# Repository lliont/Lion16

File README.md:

# Lion
Lion FPGA CPU/Computer

The Lion computer project files.

Lion CPU is a homebrew CPU and Lion Computer is a homebrew 16-bit computer based on this cpu.

lionsys.sof and lionsys.jic are the files for configuration of a QMTech Cyclone V FPGA board for Lion.

sdcard.zip contains files for the 30MB FAT partition on a SDCard for Lion to boot.

Lionasm.exe is an assembler for Lion.

Liontiny.asm is the Basic source file that when compiled and it's output Liontiny.bin is named BOOT.BIN (exists in sdcard.zip) and copied to sdcard it boots lion in tiny basic.

Lion1.sch and Lion1.brd are eagle files for the Lion base board.

Hardware design and software released under the Creative Commons License BY-NC-SA https://creativecommons.org/licenses/by-nc-sa/4.0/

Theodoulos Liontakis

Project Pages:

http://users.sch.gr/tliontakis/index.php/my-projects/13-vhdl-cpu

https://hackaday.io/project/162876-lion-fpga-cpucomputer

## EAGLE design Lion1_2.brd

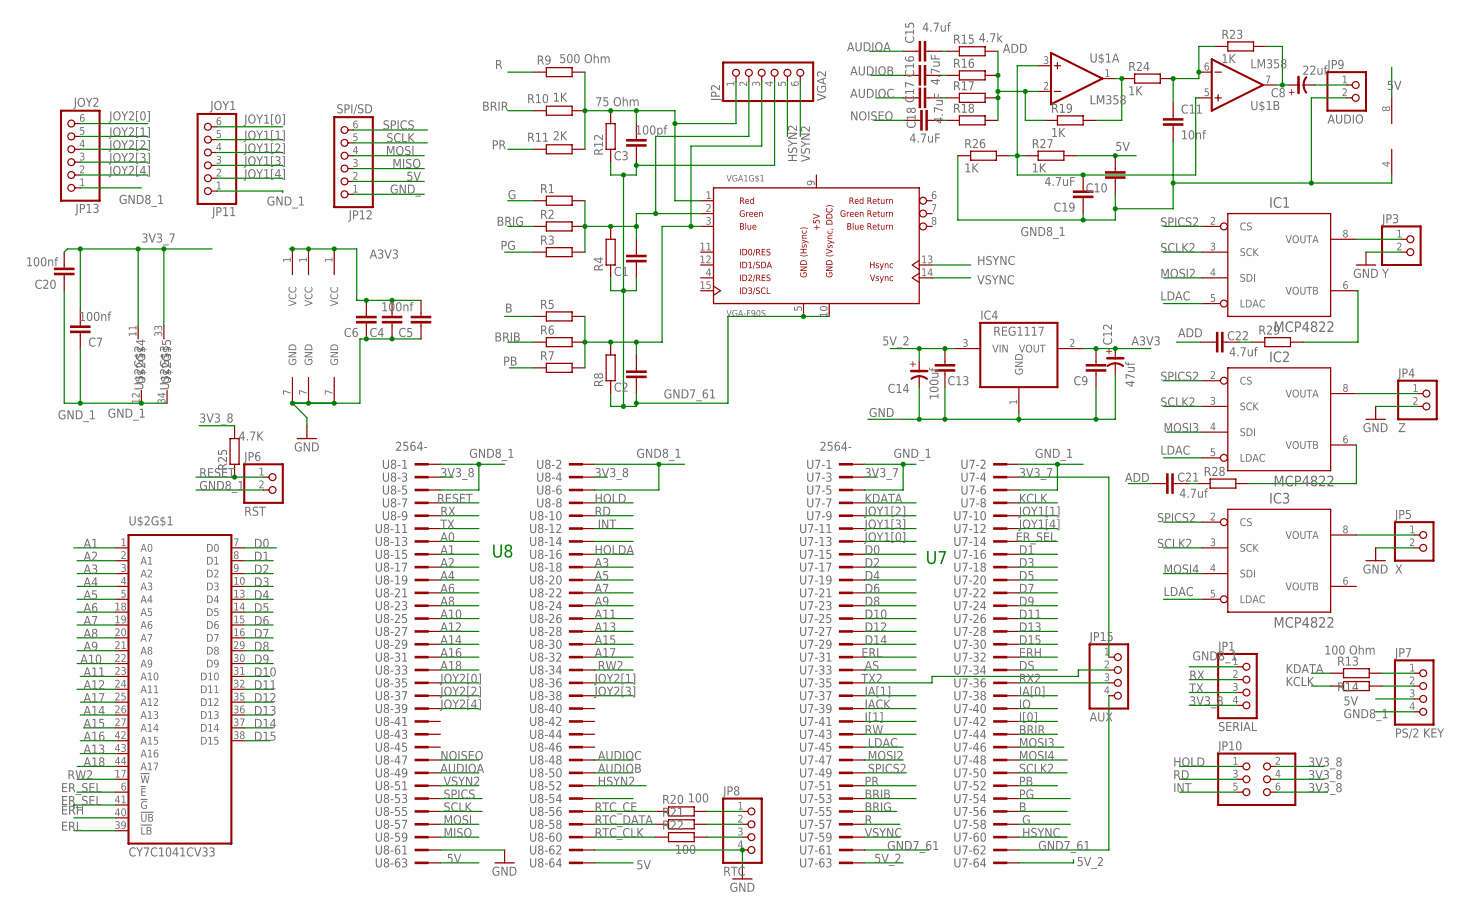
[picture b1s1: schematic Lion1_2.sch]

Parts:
C1, C2, C4, C6, C9, C10, C13: C-EU050-025X075; C050-025X075
C3: 100pf; C050-025X075
C5: 100nf; C050-025X075
C7, C20: 100nf; C0805
C8: 22uf; CE-025X060
C11: 10nf; C050-025X075
C12: 47uf; CE-025X060
C14: 100uf; CE-025X060
C15, C21, C22: 4.7uf; C050-025X075
C16, C17, C18, C19: 4.7uF; C050-025X075
IC1, IC2, IC3: MCP4822; DIL08
IC4: REG1117; SOT223
JP1: SERIAL; 1X04
JP2: VGA2; 1X06
JP3: Y; 1X02
JP4: Z; 1X02
JP5: X; 1X02
JP6: RST; 1X02
JP7: PS/2 KEY; 1X04
JP8: RTC; 1X04
JP9: AUDIO; 1X02
JP10: PINHD-2X3; 2X03
JP11: JOY1; 1X06
JP12: SPI/SD; 1X06
JP13: JOY2; 1X06
JP15: AUX; 1X04
R1, R2, R3, R4, R5, R6, R7, R8, R14, R22: R-EU_0204/7; 0204/7
R9: 500 Ohm; 0204/7
R10, R19, R23, R24, R26, R27: 1K; 0204/7
R11: 2K; 0204/7
R12: 75 Ohm; 0204/7
R13: 100 Ohm; 0204/7
R15: 4.7k; 0204V
R16, R17, R18, R28, R29: R-EU_0204/2V; 0204V
R20, R21: 100; 0204/7
R25: 4.7K; 0204/5
U7, U8: 2564-; PAK100/2500-64
U$1: LM358; DIL8
U$2: CY7C1041CV33; TSOP44-II
VGA1: VGA-F90S; DB-15-F90+SHIELD-SMALL_PADS

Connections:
3V3_7: C7.2, C20.2, JP15.1, U7.3, U7.4, U$2.11 (VCC), U$2.33 (VCC)
3V3_8: JP1.4, JP10.2, JP10.4, JP10.6, R25.2, U8.3, U8.4
5V: C10.2, JP7.3, JP12.2, R27.2, U8.63, U8.64, U$1.8 (V+)
5V_2: C13.2, C14.+, IC4.3 (VIN), U7.63, U7.64
+5V: VGA1.9 (+5V)
A0: U8.13
A1: U8.15, U$2.1 (A0)
A2: U8.17, U$2.2 (A1)
A3: U8.18, U$2.3 (A2)
A3V3: C4.2, C5.2, C6.2, C9.2, C12.+, IC1.1 (VCC), IC2.1 (VCC), IC3.1 (VCC), IC4.2 (VOUT)
A4: U8.19, U$2.4 (A3)
A5: U8.20, U$2.5 (A4)
A6: U8.21, U$2.18 (A5)
A7: U8.22, U$2.19 (A6)
A8: U8.23, U$2.20 (A7)
A9: U8.24, U$2.21 (A8)
A10: U8.25, U$2.22 (A9)
A11: U8.26, U$2.23 (A10)
A12: U8.27, U$2.24 (A11)
A13: U8.28, U$2.43 (A16)
A14: U8.29, U$2.26 (A13)
A15: U8.30, U$2.27 (A14)
A16: U8.31, U$2.42 (A15)
A17: U8.32, U$2.25 (A12)
A18: U8.33, U$2.44 (A17)
ADD: C21.1, C22.1, R15.2, R16.2, R17.2, R18.2, R19.1, U$1.2 (-IN)
AS: U7.33
AUDIOA: C15.1, U8.49
AUDIOB: C16.1, U8.50
AUDIOC: C17.1, U8.48
B: R5.1, U7.56
BRIB: R6.1, U7.53
BRIG: R2.1, U7.55
BRIR: R10.1, U7.44
D0: U7.15, U$2.7 (D0)
D1: U7.16, U$2.8 (D1)
D2: U7.17, U$2.9 (D2)
D3: U7.18, U$2.10 (D3)
D4: U7.19, U$2.13 (D4)
D5: U7.20, U$2.14 (D5)
D6: U7.21, U$2.15 (D6)
D7: U7.22, U$2.16 (D7)
D8: U7.23, U$2.29 (D8)
D9: U7.24, U$2.30 (D9)
D10: U7.25, U$2.31 (D10)
D11: U7.26, U$2.32 (D11)
D12: U7.27, U$2.35 (D12)
D13: U7.28, U$2.36 (D13)
D14: U7.29, U$2.37 (D14)
D15: U7.30, U$2.38 (D15)
DS: U7.34
ERH: U7.32, U$2.40 (!UB)
ERL: U7.31, U$2.39 (!LB)
ER_SEL: U7.14, U$2.6 (!E), U$2.41 (!G)
G: R1.1, U7.58
GND7_61: C1.1, C2.1, C3.1, JP2.4, JP15.4, R4.1, R8.1, R12.1, U7.61, U7.62, VGA1.5 (GND), VGA1.10 (GND)
GND8_1: C10.1, C11.2, C19.1, JP1.1, JP6.2, JP7.4, JP9.2, JP13.1, R26.1, U8.1, U8.2, U8.5, U8.6, U$1.4 (V-)
GND_: C4.1, C5.1, C6.1, C9.1, C12.-, C13.1, C14.-, IC1.7 (GND), IC2.7 (GND), IC3.7 (GND), IC4.1 (GND), JP3.2, JP4.2, JP5.2, JP8.4, JP12.1, U8.61, U8.62
GND_1: C7.1, C20.1, JP11.1, U7.1, U7.2, U7.5, U7.6, U$2.12 (VSS), U$2.34 (VSS)
HOLD: JP10.1, U8.8
HOLDA: U8.16
HSYN2: JP2.5, U8.52
HSYNC: U7.60, VGA1.13 (VGA-HSYNC)
IACK: U7.39
IA[0]: U7.38
IA[1]: U7.37
INT: JP10.5, U8.12
IO: U7.40
I[0]: U7.42
I[1]: U7.41
JOY1[0]: JP11.6, U7.13
JOY1[1]: JP11.5, U7.10
JOY1[2]: JP11.4, U7.9
JOY1[3]: JP11.3, U7.11
JOY1[4]: JP11.2, U7.12
JOY2[0]: JP13.6, U8.35
JOY2[1]: JP13.5, U8.36
JOY2[2]: JP13.4, U8.37
JOY2[3]: JP13.3, U8.38
JOY2[4]: JP13.2, U8.39
KCLK: R14.1, U7.8
KDATA: R13.1, U7.7
LDAC: IC1.5 (LDAC), IC2.5 (LDAC), IC3.5 (LDAC), U7.45
MISO: JP12.3, U8.59
MOSI: JP12.4, U8.57
MOSI2: IC1.4 (SDI), U7.47
MOSI3: IC2.4 (SDI), U7.46
MOSI4: IC3.4 (SDI), U7.48
unnamed: C1.2, JP2.2, R1.2, R2.2, R3.2, R4.2, VGA1.2 (VGA-G)
unnamed: IC2.6 (VOUTB), R28.2
unnamed: C19.2, R26.2, R27.1, U$1.3 (+IN), U$1.5 (+IN)
unnamed: C15.2, R15.1
unnamed: IC3.8 (VOUTA), JP5.1
unnamed: C2.2, JP2.3, R5.2, R6.2, R7.2, R8.2, VGA1.3 (VGA-B)
unnamed: IC2.8 (VOUTA), JP4.1
unnamed: IC1.8 (VOUTA), JP3.1
unnamed: C21.2, R28.1
unnamed: C3.2, JP2.1, R9.2, R10.2, R11.2, R12.2, VGA1.1 (VGA-R)
unnamed: R19.2, R24.1, U$1.1 (OUT)
unnamed: JP7.1, R13.2
unnamed: JP7.2, R14.2
unnamed: C8.-, JP9.1
unnamed: JP8.1, R20.2
unnamed: JP8.2, R21.2
unnamed: JP8.3, R22.2
unnamed: C8.+, R23.2, U$1.7 (OUT)
unnamed: C11.1, R23.1, R24.2, U$1.6 (-IN)
unnamed: C16.2, R16.1
unnamed: C17.2, R17.1
unnamed: C18.2, R18.1
unnamed: C22.2, R29.1
unnamed: IC1.6 (VOUTB), R29.2
NOISEO: C18.1, U8.47
PB: R7.1, U7.52
PG: R3.1, U7.54
PR: R11.1, U7.51
R: R9.1, U7.57
RD: JP10.3, U8.10
RESET: JP6.1, R25.1, U8.7
RTC_CE: R20.1, U8.56
RTC_CLK: R22.1, U8.60
RTC_DATA: R21.1, U8.58
RW: U7.43
RW2: U8.34, U$2.17 (!W)
RX: JP1.2, U8.9
RX2: JP15.3, U7.36
SCLK: JP12.5, U8.55
SCLK2: IC1.3 (SCK), IC2.3 (SCK), IC3.3 (SCK), U7.50
SPICS: JP12.6, U8.53
SPICS2: IC1.2 (CS), IC2.2 (CS), IC3.2 (CS), U7.49
TX: JP1.3, U8.11
TX2: JP15.2, U7.35
VSYN2: JP2.6, U8.51
VSYNC: U7.59, VGA1.14 (VGA-VSYNC)

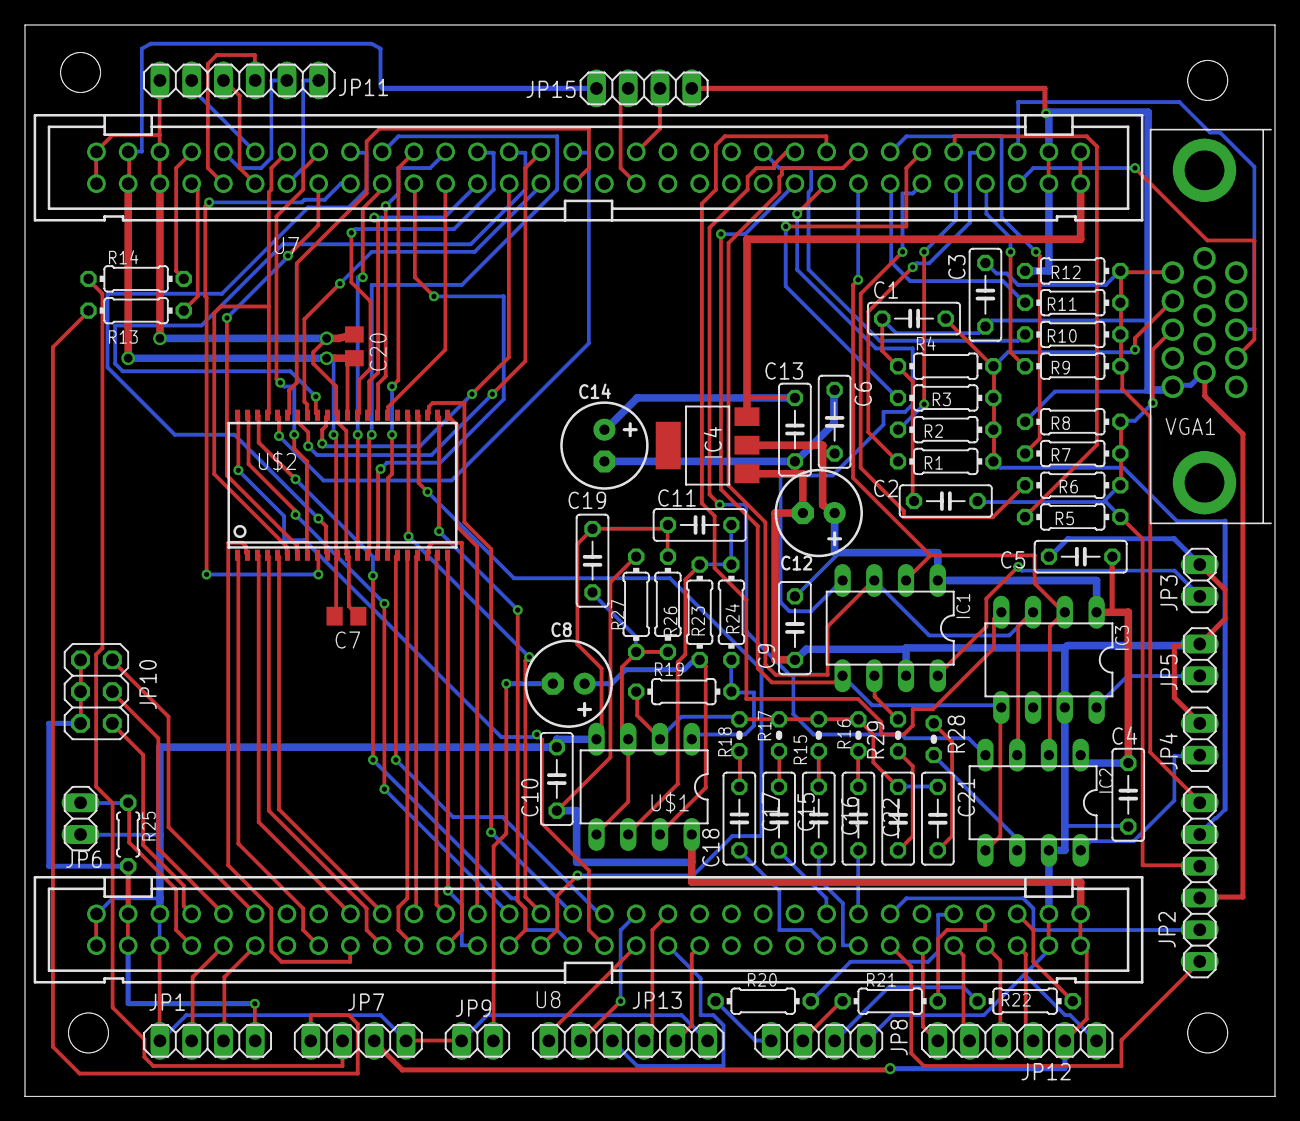
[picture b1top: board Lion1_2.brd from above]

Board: 2 copper layers, 100.0 x 85.7 mm, 74 parts (0 on the bottom side), 122 nets.

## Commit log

2021-01-05 Initial
2021-01-05 no message
2021-01-06 Sound volume fix
2021-01-06 Beep command
2021-03-01 VHDL source

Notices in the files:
parts and their libraries:
eagle-6.5.0-atari: Copyright (c) 2010
Copyright (c) 2009
This library is licensed under the
Creative Commons Attribution 3.0 United States License.
rc-master: Copyright (C) 2007, Bob Starr
